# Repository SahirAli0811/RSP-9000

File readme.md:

# <div align="center">RSP-9000 #
## <div align="center">Robotic Hand To Play Rock, Paper, Scissors ##
### <div align="center">Made by me - Tung Tung Tung Sahir ###
---
# <div align="center">--- What Is It And How It Works --- #

<p>I have made this project for maker faire in china for #fallen

<p>It is a Robotic Hand that can play Rock, Paper, Scissors with you, Cause you don't have friends lol :( </p>

<p>It uses 4 MG996r Servo motors for four fingers and uses MG90s Servo for the movement of thumb</p> 

<p> I have also built a custom pcb but i won't get it on time so i will be using Arduino Board and PWM I2C for servos movement</p>

<p>I have also custom built the whole model for the hand with arm where holder is there to hold servo motors and also made custom horns for MG996r servo motors </p>

<p>It works like you would press a button and on count of three the machine will select its move and move servo accordingly to the move and if you lose it celebrates and if you winn it flips you off</p>

---

# <div align="center">--- Custom PCB --- #
### <div align="center">--- (not used cause i won't recive before event) --- ###
### Made by Me ###

<p>Custom Schematic It uses ESP-32 S3 Wroom 1 Module with custom made servo pwm </p>

---

# <div align="center">--- Custom CAD --- #
### Made by Me ###

<p>I have made custom CAD design for the hand with CAD's of Fingers, Palm, Thumb Joint, Wrist, Forearm, Servo Holder and Servo horn </p>

<p>Here are the images </p>

---

---

# <div align="center">--- Custom Firmware --- #
### Made by Me ###

<p> For now i have made a simple custom firmware which only shows the movement of all servo after making the real build i will test and write real firmware </p>

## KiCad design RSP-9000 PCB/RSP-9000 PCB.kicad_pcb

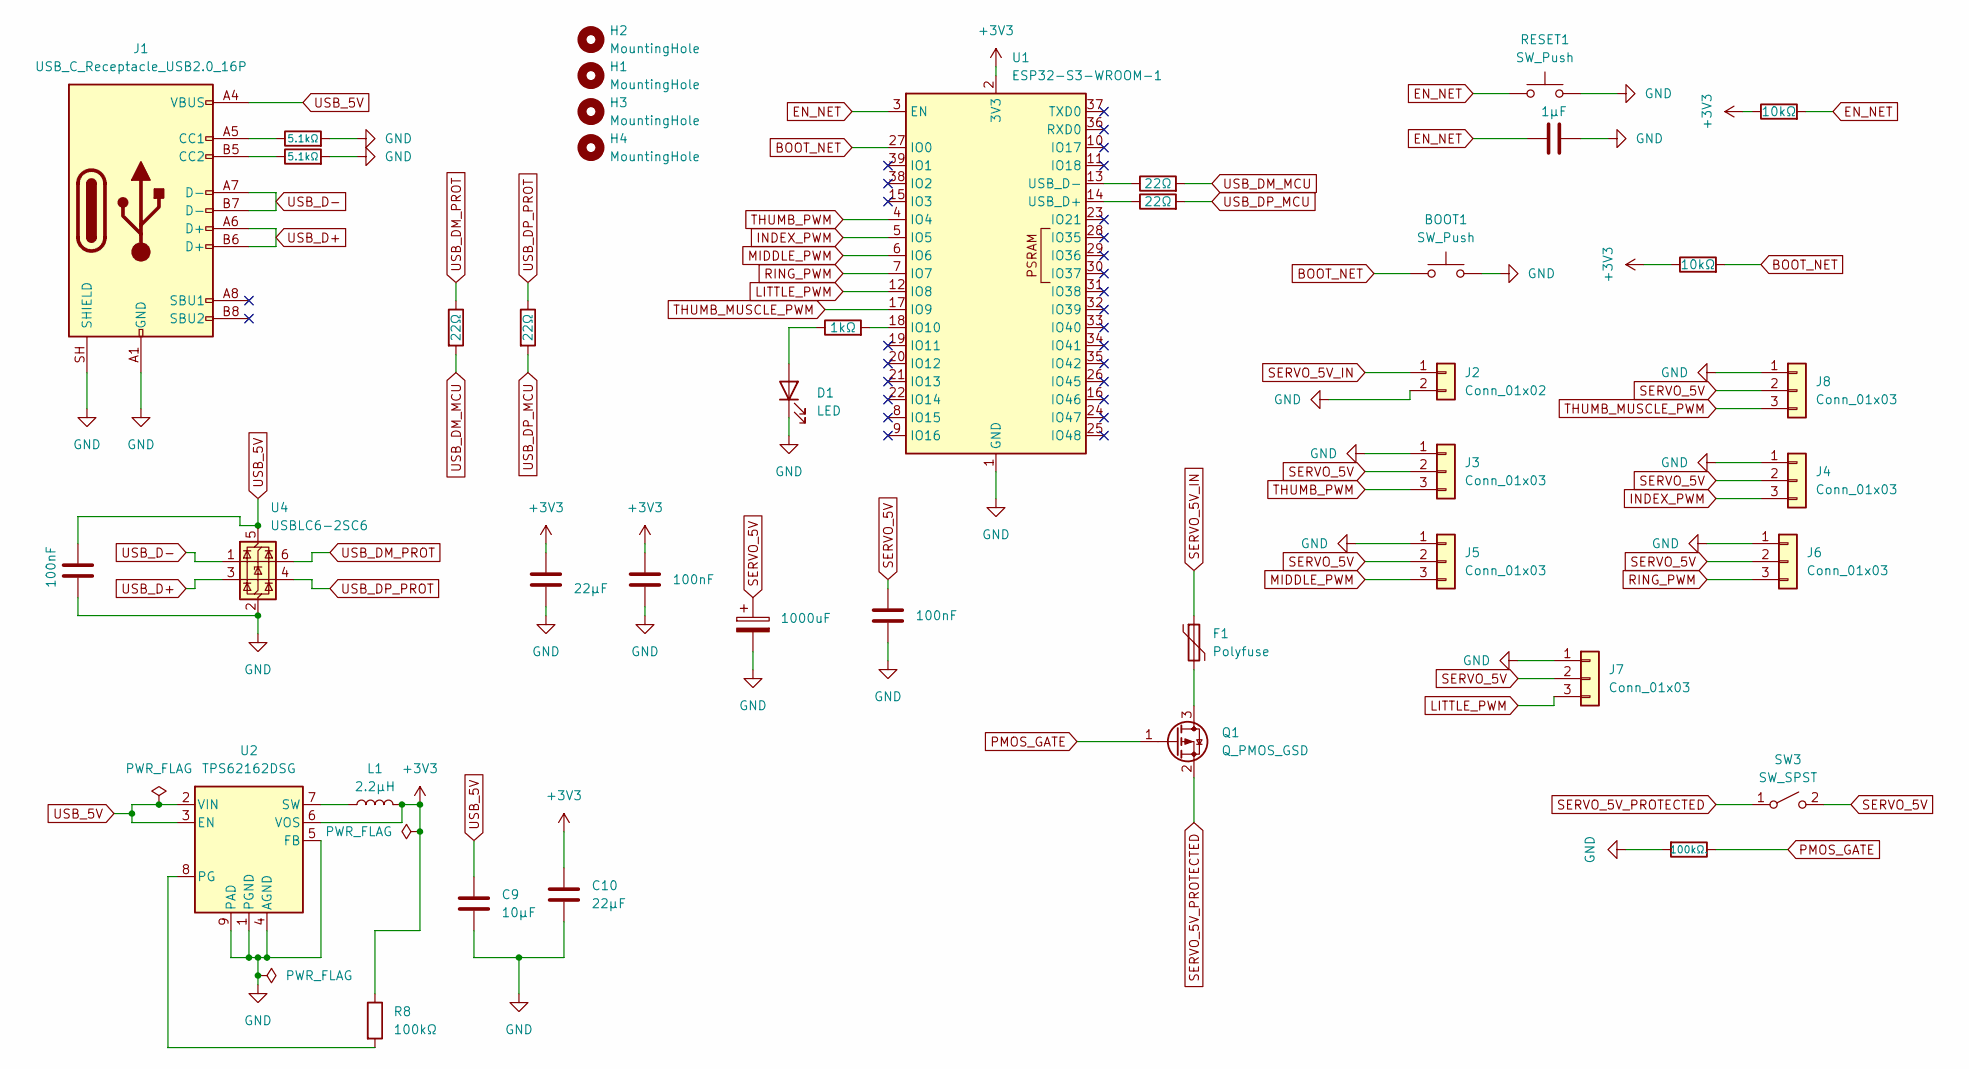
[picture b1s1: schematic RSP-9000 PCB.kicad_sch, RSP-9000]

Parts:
BOOT1: SW_Push; SW_PUSH_6mm
C1: 22µF; C_1206_3216Metric
C2, C4, C11: 100nF; C_0603_1608Metric
C3: 1000uF; CP_Radial_D10.0mm_P5.00mm
C5: 1µF; C_0805_2012Metric
C9: 10µF; C_1206_3216Metric
C10: 22µF; C_1210_3225Metric
D1: LED; LED_0805_2012Metric
F1: Polyfuse; Fuse_1206_3216Metric
H1, H2, H3, H4: MountingHole; MountingHole_2.5mm_Pad
J1: USB_C_Receptacle_USB2.0_16P; USB_C_Receptacle_HRO_TYPE-C-31-M-12
J2: Conn_01x02; TerminalBlock_Phoenix_MKDS-1,5-2_1x02_P5.00mm_Horizontal
J3, J4, J5, J6, J7, J8: Conn_01x03; PinHeader_1x03_P2.54mm_Vertical
L1: 2.2µH; IND_VLS3012CX-2R2M-1
Q1: Q_PMOS_GSD; TO-252-2
R1, R2: 5.1kΩ; R_0603_1608Metric
R3, R4, R10, R11: 22Ω; R_0603_1608Metric
R5, R6: 10kΩ; R_0603_1608Metric
R7: 1kΩ; R_0603_1608Metric
R8: 100kΩ; R_0603_1608Metric
R9: 100kΩ.; R_0603_1608Metric
RESET1: SW_Push; SW_PUSH_6mm
SW3: SW_SPST
U1: ESP32-S3-WROOM-1
U2: TPS62162DSG; Texas_DSG0008A_WSON-8-1EP_2x2mm_P0.5mm_EP0.9x1.6mm_ThermalV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
U4: USBLC6-2SC6; SOT-23-6

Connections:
+3V3: C1.1, C2.1, C10.1, L1.2, R5.1, R6.1, R8.1, U1.2 (3V3), U2.6 (VOS)
BOOT_NET: BOOT1.1, R6.2, U1.27 (IO0)
EN_NET: C5.1, R5.2, RESET1.1, U1.3 (EN)
GND: BOOT1.2, C1.2, C2.2, C3.2, C4.2, C5.2, C9.2, C10.2, C11.2, D1.1 (K), J1.A1 (GND), J1.A12 (GND), J1.B1 (GND), J1.B12 (GND), J1.SH (SHIELD), J2.2, J3.1, J4.1, J5.1, J6.1, J7.1, J8.1, R1.2, R2.2, R9.2, RESET1.2, U1.1 (GND), U1.40 (GND), U1.41 (GND), U2.1 (PGND), U2.4 (AGND), U2.5 (FB), U2.9 (PAD), U4.2 (GND)
INDEX_PWM: J4.3, U1.5 (IO5)
LITTLE_PWM: J7.3, U1.12 (IO8)
MIDDLE_PWM: J5.3, U1.6 (IO6)
unnamed: D1.2 (A), R7.1
unnamed: J1.A5 (CC1), R1.1
unnamed: J1.B5 (CC2), R2.1
unnamed: F1.2, Q1.3 (D)
unnamed: R7.2, U1.18 (IO10)
unnamed: R4.1, U1.14 (USB_D+)
unnamed: R3.1, U1.13 (USB_D-)
unnamed: R8.2, U2.8 (PG)
unnamed: L1.1, U2.7 (SW)
PMOS_GATE: Q1.1 (G), R9.1
RING_PWM: J6.3, U1.7 (IO7)
SERVO_5V: C3.1, C4.1, J3.2, J4.2, J5.2, J6.2, J7.2, J8.2, SW3.2 (B)
SERVO_5V_IN: F1.1, J2.1
SERVO_5V_PROTECTED: Q1.2 (S), SW3.1 (A)
THUMB_MUSCLE_PWM: J8.3, U1.17 (IO9)
THUMB_PWM: J3.3, U1.4 (IO4)
USB_5V: C9.1, C11.1, J1.A4 (VBUS), J1.A9 (VBUS), J1.B4 (VBUS), J1.B9 (VBUS), U2.2 (VIN), U2.3 (EN), U4.5 (VBUS)
USB_D+: J1.A6 (D+), J1.B6 (D+), U4.3 (I/O2)
USB_D-: J1.A7 (D-), J1.B7 (D-), U4.1 (I/O1)
USB_DM_MCU: R3.2, R10.2
USB_DM_PROT: R10.1, U4.6 (I/O1)
USB_DP_MCU: R4.2, R11.2
USB_DP_PROT: R11.1, U4.4 (I/O2)

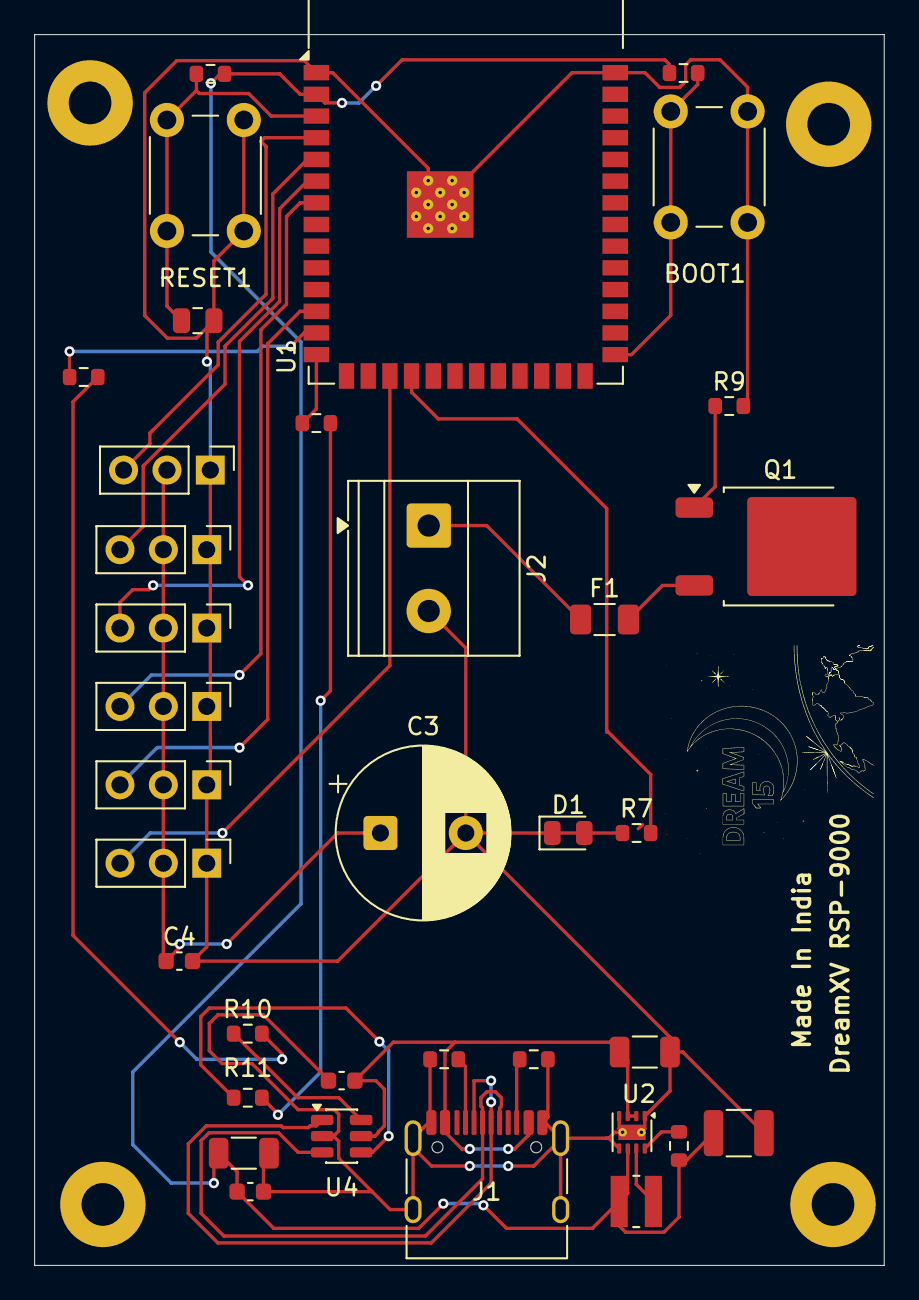
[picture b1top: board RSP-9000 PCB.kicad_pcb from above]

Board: 2 copper layers, 49.8 x 72.1 mm, 40 parts (0 on the bottom side), 29 nets.
